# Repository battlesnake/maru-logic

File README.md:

Boolean logic toy for a toddler.

Powered via USB-C (5V) off pretty much any phone charger or other USB-C power source.

Also, I decided to take a "no code" approach to this project, i.e. everything is basically analogue, including the memory and running-LED effects.

[Render](https://github.com/battlesnake/maru-logic/blob/da1b877b9f830693bbb3e6eb010e83701448b195/renders/0001.png)

TODO: Upload the demo video to the repo and add to README

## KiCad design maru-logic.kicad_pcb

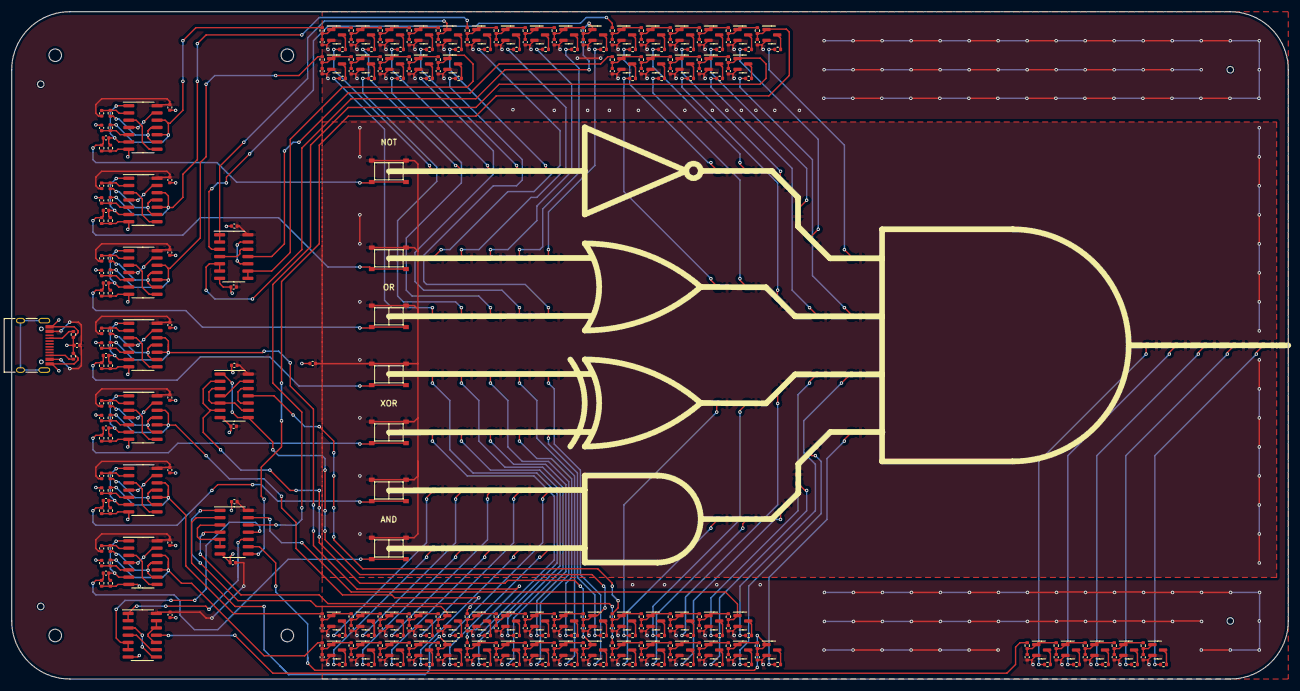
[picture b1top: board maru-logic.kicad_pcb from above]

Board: 2 copper layers, 223.5 x 116.8 mm, 404 parts (0 on the bottom side), 262 nets.

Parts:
C101, C102, C103, C104, C105, C106, C107, C108, C109, C201, C501, C701, C901, C1101, C1301, C1501: 100n; C_0402_1005Metric
C202, C203, C204, C502, C503, C504, C702, C703, C704, C902, C903, C904, C1102, C1103, C1104, C1302, C1303, C1304, C1502, C1503, C1504: 1n; C_0402_1005Metric
C401, C1701, C1801, C1901, C2001, C2101, C2201, C2301, C2401, C2501, C2601, C2701, C2801, C2901, C3001, C3201, C3301, C3401, C3501, C3601, C3701, C3801, C3901, C4001, C4301, C4501, C4601, C4701, C4801, C4901, C5001, C5101, C5201, C5301, C5501, C5601, C5701, C5801, C5901, C6101, C6201, C6301, C6401, C6501, C6701, C6801, C6901, C7001, C7101, C7401, C7501, C7601, C7701, C7801, C8001, C8101, C9801, C9901, C10001, C10101, C10201, C10301: 1u; C_0402_1005Metric
D401, D1701, D1801, D1901, D2001, D2101, D2201, D2301, D2401, D2501, D2601, D2701, D2801, D2901, D3001, D3201, D3301, D3401, D3501, D3601, D3701, D3801, D3901, D4001, D4301, D4501, D4601, D4701, D4801, D4901, D5001, D5101, D5201, D5301, D5501, D5601, D5701, D5801, D5901, D6101, D6201, D6301, D6401, D6501, D6701, D6801, D6901, D7001, D7101, D7401, D7501, D7601, D7701, D7801, D8001, D8101, D9801, D9901, D10001, D10101, D10201, D10301: White; LED_0603_1608Metric_no_silk
H101, H102, H105, H106: JLC; JLCPCB_ToolingHole_1152_1300_1400_1650
H103, H104, H107, H108: MountingHole; MountingHole_2.2mm_M2_ISO7380
J101: USB-C; USB_C_Receptacle_HRO_TYPE-C-31-M-12
Q401, Q1701, Q1801, Q1901, Q2001, Q2101, Q2201, Q2301, Q2401, Q2501, Q2601, Q2701, Q2801, Q2901, Q3001, Q3201, Q3301, Q3401, Q3501, Q3601, Q3701, Q3801, Q3901, Q4001, Q4301, Q4501, Q4601, Q4701, Q4801, Q4901, Q5001, Q5101, Q5201, Q5301, Q5501, Q5601, Q5701, Q5801, Q5901, Q6101, Q6201, Q6301, Q6401, Q6501, Q6701, Q6801, Q6901, Q7001, Q7101, Q7401, Q7501, Q7601, Q7701, Q7801, Q8001, Q8101, Q9801, Q9901, Q10001, Q10101, Q10201, Q10301: 2N7002; SOT-23
R101, R102: 5.1k; R_0402_1005Metric
R201, R501, R701, R901, R1101, R1301, R1501: 1M; R_0402_1005Metric
R202, R502, R702, R902, R1102, R1302, R1502: 1k; R_0402_1005Metric
R203, R204, R503, R504, R703, R704, R903, R904, R1103, R1104, R1303, R1304, R1503, R1504: 10k; R_0402_1005Metric
R401, R1701, R1801, R1901, R2001, R2101, R2201, R2301, R2401, R2501, R2601, R2701, R2801, R2901, R3001, R3201, R3301, R3401, R3501, R3601, R3701, R3801, R3901, R4001, R4301, R4501, R4601, R4701, R4801, R4901, R5001, R5101, R5201, R5301, R5501, R5601, R5701, R5801, R5901, R6101, R6201, R6301, R6401, R6501, R6701, R6801, R6901, R7001, R7101, R7401, R7501, R7601, R7701, R7801, R8001, R8101, R9801, R9901, R10001, R10101, R10201, R10301: 100k; R_0402_1005Metric
R402, R1702, R1802, R1902, R2002, R2102, R2202, R2302, R2402, R2502, R2602, R2702, R2802, R2902, R3002, R3202, R3302, R3402, R3502, R3602, R3702, R3802, R3902, R4002, R4302, R4502, R4602, R4702, R4802, R4902, R5002, R5102, R5202, R5302, R5502, R5602, R5702, R5802, R5902, R6102, R6202, R6302, R6402, R6502, R6702, R6802, R6902, R7002, R7102, R7402, R7502, R7602, R7702, R7802, R8002, R8102, R9802, R9902, R10002, R10102, R10202, R10302: 220; R_0402_1005Metric
SW301, SW601, SW801, SW1001, SW1201, SW1401, SW1601: Push; jlc_pushbutton
U101, U102, U103, U104, U201, U501, U701, U901, U1101, U1301, U1501: 4093; SOIC-14_3.9x8.7mm_P1.27mm

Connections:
/ALL_X: R1801.1, U104.11
/ALL_Y: C2101.1, Q2101.1 (G), R2101.2
/AND_A: C7101.1, Q7101.1 (G), R7101.2, U103.1
/AND_B: C7801.1, Q7801.1 (G), R7801.2, U103.2
/AND_X: R4701.1, U103.4
/AND_Y: C4901.1, Q4901.1 (G), R4901.2, U103.9
/BAA: R504.1, R6901.1, U501.10, U501.12
/BAB: R704.1, R7601.1, U701.10, U701.12
/BNA: R204.1, R2801.1, U201.10, U201.12
/BOA: R904.1, R3601.1, U901.10, U901.12
/BOB: R1104.1, R3901.1, U1101.10, U1101.12
/BXA: R1304.1, R5701.1, U1301.10, U1301.12
/BXB: R1504.1, R6301.1, U1501.10, U1501.12
/Button AND_A/T flip-flop/PULSE: C502.2, R502.2, U501.1, U501.6
/Button AND_A/T flip-flop/Q': C504.1, R504.2, U501.5
/Button AND_A/T flip-flop/RESET: U501.4, U501.13
/Button AND_A/T flip-flop/SET: U501.3, U501.8
/Button AND_A/T flip-flop/TOGGLE: C502.1, R501.2, SW601.2
/Button AND_A/T flip-flop/~Q: R503.1, U501.9, U501.11
/Button AND_A/T flip-flop/~Q': C503.2, R503.2, U501.2
/Button AND_B/T flip-flop/PULSE: C702.2, R702.2, U701.1, U701.6
/Button AND_B/T flip-flop/Q': C704.1, R704.2, U701.5
/Button AND_B/T flip-flop/RESET: U701.4, U701.13
/Button AND_B/T flip-flop/SET: U701.3, U701.8
/Button AND_B/T flip-flop/TOGGLE: C702.1, R701.2, SW801.2
/Button AND_B/T flip-flop/~Q: R703.1, U701.9, U701.11
/Button AND_B/T flip-flop/~Q': C703.2, R703.2, U701.2
/Button NOT_A/T flip-flop/PULSE: C202.2, R202.2, U201.1, U201.6
/Button NOT_A/T flip-flop/Q': C204.1, R204.2, U201.5
/Button NOT_A/T flip-flop/RESET: U201.4, U201.13
/Button NOT_A/T flip-flop/SET: U201.3, U201.8
/Button NOT_A/T flip-flop/TOGGLE: C202.1, R201.2, SW301.2
/Button NOT_A/T flip-flop/~Q: R203.1, U201.9, U201.11
/Button NOT_A/T flip-flop/~Q': C203.2, R203.2, U201.2
/Button OR_A/T flip-flop/PULSE: C902.2, R902.2, U901.1, U901.6
/Button OR_A/T flip-flop/Q': C904.1, R904.2, U901.5
/Button OR_A/T flip-flop/RESET: U901.4, U901.13
/Button OR_A/T flip-flop/SET: U901.3, U901.8
/Button OR_A/T flip-flop/TOGGLE: C902.1, R901.2, SW1001.2
/Button OR_A/T flip-flop/~Q: R903.1, U901.9, U901.11
/Button OR_A/T flip-flop/~Q': C903.2, R903.2, U901.2
/Button OR_B/T flip-flop/PULSE: C1102.2, R1102.2, U1101.1, U1101.6
/Button OR_B/T flip-flop/Q': C1104.1, R1104.2, U1101.5
/Button OR_B/T flip-flop/RESET: U1101.4, U1101.13
/Button OR_B/T flip-flop/SET: U1101.3, U1101.8
/Button OR_B/T flip-flop/TOGGLE: C1102.1, R1101.2, SW1201.2
/Button OR_B/T flip-flop/~Q: R1103.1, U1101.9, U1101.11
/Button OR_B/T flip-flop/~Q': C1103.2, R1103.2, U1101.2
/Button XOR_A/T flip-flop/PULSE: C1302.2, R1302.2, U1301.1, U1301.6
/Button XOR_A/T flip-flop/Q': C1304.1, R1304.2, U1301.5
/Button XOR_A/T flip-flop/RESET: U1301.4, U1301.13
/Button XOR_A/T flip-flop/SET: U1301.3, U1301.8
/Button XOR_A/T flip-flop/TOGGLE: C1302.1, R1301.2, SW1401.2
/Button XOR_A/T flip-flop/~Q: R1303.1, U1301.9, U1301.11
/Button XOR_A/T flip-flop/~Q': C1303.2, R1303.2, U1301.2
/Button XOR_B/T flip-flop/PULSE: C1502.2, R1502.2, U1501.1, U1501.6
/Button XOR_B/T flip-flop/Q': C1504.1, R1504.2, U1501.5
/Button XOR_B/T flip-flop/RESET: U1501.4, U1501.13
/Button XOR_B/T flip-flop/SET: U1501.3, U1501.8
/Button XOR_B/T flip-flop/TOGGLE: C1502.1, R1501.2, SW1601.2
/Button XOR_B/T flip-flop/~Q: R1503.1, U1501.9, U1501.11
/Button XOR_B/T flip-flop/~Q': C1503.2, R1503.2, U1501.2
/Chain ALL_X/LINK1: C1801.1, Q1801.1 (G), R401.1, R1801.2
/Chain ALL_X/LINK2: C401.1, Q401.1 (G), R401.2, R1701.1
/Chain ALL_X/LINK3: C1701.1, Q1701.1 (G), R1701.2, R1901.1
/Chain ALL_X/LINK4: C1901.1, Q1901.1 (G), R1901.2, R2101.1
/Chain AND_A/LINK1: C6901.1, Q6901.1 (G), R6701.1, R6901.2
/Chain AND_A/LINK2: C6701.1, Q6701.1 (G), R6701.2, R6801.1
/Chain AND_A/LINK3: C6801.1, Q6801.1 (G), R6801.2, R7001.1
/Chain AND_A/LINK4: C7001.1, Q7001.1 (G), R7001.2, R7101.1
/Chain AND_B/LINK1: C7601.1, Q7601.1 (G), R7401.1, R7601.2
/Chain AND_B/LINK2: C7401.1, Q7401.1 (G), R7401.2, R7501.1
/Chain AND_B/LINK3: C7501.1, Q7501.1 (G), R7501.2, R7701.1
/Chain AND_B/LINK4: C7701.1, Q7701.1 (G), R7701.2, R7801.1
/Chain AND_X/LINK1: C4701.1, Q4701.1 (G), R4601.1, R4701.2
/Chain AND_X/LINK2: C4601.1, Q4601.1 (G), R4501.1, R4601.2
/Chain AND_X/LINK3: C4501.1, Q4501.1 (G), R4501.2, R5001.1
/Chain AND_X/LINK4: C5001.1, Q5001.1 (G), R4801.1, R5001.2
/Chain AND_X/LINK5: C4801.1, Q4801.1 (G), R4801.2, R4901.1
/Chain NOT_A/LINK1: C2801.1, Q2801.1 (G), R2601.1, R2801.2
/Chain NOT_A/LINK2: C2601.1, Q2601.1 (G), R2601.2, R2701.1
/Chain NOT_A/LINK3: C2701.1, Q2701.1 (G), R2701.2, R2901.1
/Chain NOT_A/LINK4: C2901.1, Q2901.1 (G), R2901.2, R3001.1
/Chain NOT_X/LINK1: C9801.1, Q9801.1 (G), R9801.2, R9901.1
/Chain NOT_X/LINK2: C9901.1, Q9901.1 (G), R9901.2, R10001.1
/Chain NOT_X/LINK3: C10001.1, Q10001.1 (G), R10001.2, R10101.1
/Chain NOT_X/LINK4: C10101.1, Q10101.1 (G), R10101.2, R10201.1
/Chain NOT_X/LINK5: C10201.1, Q10201.1 (G), R10201.2, R10301.1
/Chain OR_A/LINK1: C3601.1, Q3601.1 (G), R3401.1, R3601.2
/Chain OR_A/LINK2: C3401.1, Q3401.1 (G), R3401.2, R3501.1
/Chain OR_A/LINK3: C3501.1, Q3501.1 (G), R3501.2, R3701.1
/Chain OR_A/LINK4: C3701.1, Q3701.1 (G), R3701.2, R3801.1
/Chain OR_B/LINK1: C3901.1, Q3901.1 (G), R3201.1, R3901.2
/Chain OR_B/LINK2: C3201.1, Q3201.1 (G), R3201.2, R3301.1
/Chain OR_B/LINK3: C3301.1, Q3301.1 (G), R3301.2, R4001.1
/Chain OR_B/LINK4: C4001.1, Q4001.1 (G), R4001.2, R5301.1
/Chain OR_X/LINK1: C2301.1, Q2301.1 (G), R2001.1, R2301.2
/Chain OR_X/LINK2: C2001.1, Q2001.1 (G), R2001.2, R2201.1
/Chain OR_X/LINK3: C2201.1, Q2201.1 (G), R2201.2, R2401.1
/Chain OR_X/LINK4: C2401.1, Q2401.1 (G), R2401.2, R2501.1
/Chain XOR_A/LINK1: C5701.1, Q5701.1 (G), R5501.1, R5701.2
/Chain XOR_A/LINK2: C5501.1, Q5501.1 (G), R5501.2, R5601.1
/Chain XOR_A/LINK3: C5601.1, Q5601.1 (G), R5601.2, R5801.1
/Chain XOR_A/LINK4: C5801.1, Q5801.1 (G), R5801.2, R5901.1
/Chain XOR_B/LINK1: C6301.1, Q6301.1 (G), R6101.1, R6301.2
/Chain XOR_B/LINK2: C6101.1, Q6101.1 (G), R6101.2, R6201.1
/Chain XOR_B/LINK3: C6201.1, Q6201.1 (G), R6201.2, R6401.1
/Chain XOR_B/LINK4: C6401.1, Q6401.1 (G), R6401.2, R6501.1
/Chain XOR_X/LINK1: C5201.1, Q5201.1 (G), R4301.1, R5201.2
/Chain XOR_X/LINK2: C4301.1, Q4301.1 (G), R4301.2, R5101.1
/Chain XOR_X/LINK3: C5101.1, Q5101.1 (G), R5101.2, R8001.1
/Chain XOR_X/LINK4: C8001.1, Q8001.1 (G), R8001.2, R8101.1
/NOT_A: C3001.1, Q3001.1 (G), R3001.2, U101.1, U101.2
/NOT_X: R9801.1, U101.3
/NOT_Y: C10301.1, Q10301.1 (G), R10301.2, U103.8
/OR_A: C3801.1, Q3801.1 (G), R3801.2, U101.5, U101.6
/OR_B: C5301.1, Q5301.1 (G), R5301.2, U101.8, U101.9
/OR_X: R2301.1, U101.11
/OR_Y: C2501.1, Q2501.1 (G), R2501.2, U103.12
/XOR_A: C5901.1, Q5901.1 (G), R5901.2, U102.2, U102.6
/XOR_B: C6501.1, Q6501.1 (G), R6501.2, U102.1, U102.8
/XOR_X: R5201.1, U102.11
/XOR_Y: C8101.1, Q8101.1 (G), R8101.2, U103.13
unnamed: D401.1 (K), R402.1
unnamed: D1701.1 (K), R1702.1
unnamed: D1801.1 (K), R1802.1
unnamed: D1901.1 (K), R1902.1
unnamed: D2001.1 (K), R2002.1
unnamed: D2101.1 (K), R2102.1
unnamed: D2201.1 (K), R2202.1
unnamed: D2301.1 (K), R2302.1
unnamed: D2401.1 (K), R2402.1
unnamed: D2501.1 (K), R2502.1
unnamed: D2601.1 (K), R2602.1
unnamed: D2701.1 (K), R2702.1
unnamed: D2801.1 (K), R2802.1
unnamed: D2901.1 (K), R2902.1
unnamed: D3001.1 (K), R3002.1
unnamed: D3201.1 (K), R3202.1
unnamed: D3301.1 (K), R3302.1
unnamed: D3401.1 (K), R3402.1
unnamed: D3501.1 (K), R3502.1
unnamed: D3601.1 (K), R3602.1
unnamed: D3701.1 (K), R3702.1
unnamed: D3801.1 (K), R3802.1
unnamed: D3901.1 (K), R3902.1
unnamed: D4001.1 (K), R4002.1
unnamed: D4301.1 (K), R4302.1
unnamed: D4501.1 (K), R4502.1
unnamed: D4601.1 (K), R4602.1
unnamed: D4701.1 (K), R4702.1
unnamed: D4801.1 (K), R4802.1
unnamed: D4901.1 (K), R4902.1
unnamed: D5001.1 (K), R5002.1
unnamed: D5101.1 (K), R5102.1
unnamed: D5201.1 (K), R5202.1
unnamed: D5301.1 (K), R5302.1
unnamed: D5501.1 (K), R5502.1
unnamed: D5601.1 (K), R5602.1
unnamed: D5701.1 (K), R5702.1
unnamed: D5801.1 (K), R5802.1
unnamed: D5901.1 (K), R5902.1
unnamed: D6101.1 (K), R6102.1
unnamed: D6201.1 (K), R6202.1
unnamed: D6301.1 (K), R6302.1
unnamed: D6401.1 (K), R6402.1
unnamed: D6501.1 (K), R6502.1
unnamed: D6701.1 (K), R6702.1
unnamed: D6801.1 (K), R6802.1
unnamed: D6901.1 (K), R6902.1
unnamed: D7001.1 (K), R7002.1
unnamed: D7101.1 (K), R7102.1
unnamed: D7401.1 (K), R7402.1
unnamed: D7501.1 (K), R7502.1
unnamed: D7601.1 (K), R7602.1
unnamed: D7701.1 (K), R7702.1
unnamed: D7801.1 (K), R7802.1
unnamed: D8001.1 (K), R8002.1
unnamed: D8101.1 (K), R8102.1
unnamed: D9801.1 (K), R9802.1
unnamed: D9901.1 (K), R9902.1
unnamed: D10001.1 (K), R10002.1
unnamed: D10101.1 (K), R10102.1
unnamed: D10201.1 (K), R10202.1
unnamed: D10301.1 (K), R10302.1
unnamed: J101.A5 (CC1), R101.1
unnamed: J101.B5 (CC2), R102.1
unnamed: Q401.3 (D), R402.2
unnamed: Q1701.3 (D), R1702.2
unnamed: Q1801.3 (D), R1802.2
unnamed: Q1901.3 (D), R1902.2
unnamed: Q2001.3 (D), R2002.2
unnamed: Q2101.3 (D), R2102.2
unnamed: Q2201.3 (D), R2202.2
unnamed: Q2301.3 (D), R2302.2
unnamed: Q2401.3 (D), R2402.2
unnamed: Q2501.3 (D), R2502.2
unnamed: Q2601.3 (D), R2602.2
unnamed: Q2701.3 (D), R2702.2
unnamed: Q2801.3 (D), R2802.2
unnamed: Q2901.3 (D), R2902.2
unnamed: Q3001.3 (D), R3002.2
unnamed: Q3201.3 (D), R3202.2
unnamed: Q3301.3 (D), R3302.2
unnamed: Q3401.3 (D), R3402.2
unnamed: Q3501.3 (D), R3502.2
unnamed: Q3601.3 (D), R3602.2
unnamed: Q3701.3 (D), R3702.2
unnamed: Q3801.3 (D), R3802.2
unnamed: Q3901.3 (D), R3902.2
unnamed: Q4001.3 (D), R4002.2
unnamed: Q4301.3 (D), R4302.2
unnamed: Q4501.3 (D), R4502.2
unnamed: Q4601.3 (D), R4602.2
unnamed: Q4701.3 (D), R4702.2
unnamed: Q4801.3 (D), R4802.2
unnamed: Q4901.3 (D), R4902.2
unnamed: Q5001.3 (D), R5002.2
unnamed: Q5101.3 (D), R5102.2
unnamed: Q5201.3 (D), R5202.2
unnamed: Q5301.3 (D), R5302.2
unnamed: Q5501.3 (D), R5502.2
unnamed: Q5601.3 (D), R5602.2
unnamed: Q5701.3 (D), R5702.2
unnamed: Q5801.3 (D), R5802.2
unnamed: Q5901.3 (D), R5902.2
unnamed: Q6101.3 (D), R6102.2
unnamed: Q6201.3 (D), R6202.2
unnamed: Q6301.3 (D), R6302.2
unnamed: Q6401.3 (D), R6402.2
unnamed: Q6501.3 (D), R6502.2
unnamed: Q6701.3 (D), R6702.2
unnamed: Q6801.3 (D), R6802.2
unnamed: Q6901.3 (D), R6902.2
unnamed: Q7001.3 (D), R7002.2
unnamed: Q7101.3 (D), R7102.2
unnamed: Q7401.3 (D), R7402.2
unnamed: Q7501.3 (D), R7502.2
unnamed: Q7601.3 (D), R7602.2
unnamed: Q7701.3 (D), R7702.2
unnamed: Q7801.3 (D), R7802.2
unnamed: Q8001.3 (D), R8002.2
unnamed: Q8101.3 (D), R8102.2
unnamed: Q9801.3 (D), R9802.2
unnamed: Q9901.3 (D), R9902.2
unnamed: Q10001.3 (D), R10002.2
unnamed: Q10101.3 (D), R10102.2
unnamed: Q10201.3 (D), R10202.2
unnamed: Q10301.3 (D), R10302.2
unnamed: U101.10, U101.13
unnamed: U101.4, U101.12
unnamed: U102.3, U102.5, U102.9
unnamed: U102.10, U102.12
unnamed: U102.4, U102.13
unnamed: U103.3, U103.5, U103.6
unnamed: U103.10, U104.1, U104.2
unnamed: U103.11, U104.5, U104.6
unnamed: U104.3, U104.8
unnamed: U104.4, U104.9
unnamed: U104.10, U104.12, U104.13
VDD: C101.1, C102.1, C103.1, C104.1, C105.1, C106.1, C107.1, C108.1, C109.1, C201.1, C203.1, C501.1, C503.1, C701.1, C703.1, C901.1, C903.1, C1101.1, C1103.1, C1301.1, C1303.1, C1501.1, C1503.1, D401.2 (A), D1701.2 (A), D1801.2 (A), D1901.2 (A), D2001.2 (A), D2101.2 (A), D2201.2 (A), D2301.2 (A), D2401.2 (A), D2501.2 (A), D2601.2 (A), D2701.2 (A), D2801.2 (A), D2901.2 (A), D3001.2 (A), D3201.2 (A), D3301.2 (A), D3401.2 (A), D3501.2 (A), D3601.2 (A), D3701.2 (A), D3801.2 (A), D3901.2 (A), D4001.2 (A), D4301.2 (A), D4501.2 (A), D4601.2 (A), D4701.2 (A), D4801.2 (A), D4901.2 (A), D5001.2 (A), D5101.2 (A), D5201.2 (A), D5301.2 (A), D5501.2 (A), D5601.2 (A), D5701.2 (A), D5801.2 (A), D5901.2 (A), D6101.2 (A), D6201.2 (A), D6301.2 (A), D6401.2 (A), D6501.2 (A), D6701.2 (A), D6801.2 (A), D6901.2 (A), D7001.2 (A), D7101.2 (A), D7401.2 (A), D7501.2 (A), D7601.2 (A), D7701.2 (A), D7801.2 (A), D8001.2 (A), D8101.2 (A), D9801.2 (A), D9901.2 (A), D10001.2 (A), D10101.2 (A), D10201.2 (A), D10301.2 (A), J101.A4 (VBUS), J101.A9 (VBUS), J101.B4 (VBUS), J101.B9 (VBUS), SW301.1, SW601.1, SW801.1, SW1001.1, SW1201.1, SW1401.1, SW1601.1, U101.14 (VCC), U102.14 (VCC), U103.14 (VCC), U104.14 (VCC), U201.14 (VCC), U501.14 (VCC), U701.14 (VCC), U901.14 (VCC), U1101.14 (VCC), U1301.14 (VCC), U1501.14 (VCC)
VSS: C101.2, C102.2, C103.2, C104.2, C105.2, C106.2, C107.2, C108.2, C109.2, C201.2, C204.2, C401.2, C501.2, C504.2, C701.2, C704.2, C901.2, C904.2, C1101.2, C1104.2, C1301.2, C1304.2, C1501.2, C1504.2, C1701.2, C1801.2, C1901.2, C2001.2, C2101.2, C2201.2, C2301.2, C2401.2, C2501.2, C2601.2, C2701.2, C2801.2, C2901.2, C3001.2, C3201.2, C3301.2, C3401.2, C3501.2, C3601.2, C3701.2, C3801.2, C3901.2, C4001.2, C4301.2, C4501.2, C4601.2, C4701.2, C4801.2, C4901.2, C5001.2, C5101.2, C5201.2, C5301.2, C5501.2, C5601.2, C5701.2, C5801.2, C5901.2, C6101.2, C6201.2, C6301.2, C6401.2, C6501.2, C6701.2, C6801.2, C6901.2, C7001.2, C7101.2, C7401.2, C7501.2, C7601.2, C7701.2, C7801.2, C8001.2, C8101.2, C9801.2, C9901.2, C10001.2, C10101.2, C10201.2, C10301.2, J101.A1 (GND), J101.A12 (GND), J101.B1 (GND), J101.B12 (GND), Q401.2 (S), Q1701.2 (S), Q1801.2 (S), Q1901.2 (S), Q2001.2 (S), Q2101.2 (S), Q2201.2 (S), Q2301.2 (S), Q2401.2 (S), Q2501.2 (S), Q2601.2 (S), Q2701.2 (S), Q2801.2 (S), Q2901.2 (S), Q3001.2 (S), Q3201.2 (S), Q3301.2 (S), Q3401.2 (S), Q3501.2 (S), Q3601.2 (S), Q3701.2 (S), Q3801.2 (S), Q3901.2 (S), Q4001.2 (S), Q4301.2 (S), Q4501.2 (S), Q4601.2 (S), Q4701.2 (S), Q4801.2 (S), Q4901.2 (S), Q5001.2 (S), Q5101.2 (S), Q5201.2 (S), Q5301.2 (S), Q5501.2 (S), Q5601.2 (S), Q5701.2 (S), Q5801.2 (S), Q5901.2 (S), Q6101.2 (S), Q6201.2 (S), Q6301.2 (S), Q6401.2 (S), Q6501.2 (S), Q6701.2 (S), Q6801.2 (S), Q6901.2 (S), Q7001.2 (S), Q7101.2 (S), Q7401.2 (S), Q7501.2 (S), Q7601.2 (S), Q7701.2 (S), Q7801.2 (S), Q8001.2 (S), Q8101.2 (S), Q9801.2 (S), Q9901.2 (S), Q10001.2 (S), Q10101.2 (S), Q10201.2 (S), Q10301.2 (S), R101.2, R102.2, R201.1, R202.1, R501.1, R502.1, R701.1, R702.1, R901.1, R902.1, R1101.1, R1102.1, R1301.1, R1302.1, R1501.1, R1502.1, U101.7 (GND), U102.7 (GND), U103.7 (GND), U104.7 (GND), U201.7 (GND), U501.7 (GND), U701.7 (GND), U901.7 (GND), U1101.7 (GND), U1301.7 (GND), U1501.7 (GND)

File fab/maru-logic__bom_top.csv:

"Comment","Designator","Footprint","LCSC Part Number"
"1k","R1102 R1302 R1502 R202 R502 R702 R902","0402","C11702"
"1n","C1102 C1103 C1104 C1302 C1303 C1304 C1502 C1503 C1504 C202 C203 C204 C502 C503 C504 C702 C703 C704 C902 C903 C904","0402","C1523"
"100n","C101 C102 C103 C104 C105 C106 C107 C108 C109 C1101 C1301 C1501 C201 C501 C701 C901","0402","C1525"
"USB-C","J101","USB_C_Receptacle_HRO_TYPE-C-31-M-12","C165948"
"4093","U101 U102 U103 U104 U1101 U1301 U1501 U201 U501 U701 U901","SOIC-14_3.9x8.7mm_P1.27mm","C194332"
"White","D10001 D10101 D10201 D10301 D1701 D1801 D1901 D2001 D2101 D2201 D2301 D2401 D2501 D2601 D2701 D2801 D2901 D3001 D3201 D3301 D3401 D3501 D3601 D3701 D3801 D3901 D4001 D401 D4301 D4501 D4601 D4701 D4801 D4901 D5001 D5101 D5201 D5301 D5501 D5601 D5701 D5801 D5901 D6101 D6201 D6301 D6401 D6501 D6701 D6801 D6901 D7001 D7101 D7401 D7501 D7601 D7701 D7801 D8001 D8101 D9801 D9901","LED_0603_1608Metric_no_silk","C2290"
"220","R10002 R10102 R10202 R10302 R1702 R1802 R1902 R2002 R2102 R2202 R2302 R2402 R2502 R2602 R2702 R2802 R2902 R3002 R3202 R3302 R3402 R3502 R3602 R3702 R3802 R3902 R4002 R402 R4302 R4502 R4602 R4702 R4802 R4902 R5002 R5102 R5202 R5302 R5502 R5602 R5702 R5802 R5902 R6102 R6202 R6302 R6402 R6502 R6702 R6802 R6902 R7002 R7102 R7402 R7502 R7602 R7702 R7802 R8002 R8102 R9802 R9902","0402","C25091"
"100k","R10001 R10101 R10201 R10301 R1701 R1801 R1901 R2001 R2101 R2201 R2301 R2401 R2501 R2601 R2701 R2801 R2901 R3001 R3201 R3301 R3401 R3501 R3601 R3701 R3801 R3901 R4001 R401 R4301 R4501 R4601 R4701 R4801 R4901 R5001 R5101 R5201 R5301 R5501 R5601 R5701 R5801 R5901 R6101 R6201 R6301 R6401 R6501 R6701 R6801 R6901 R7001 R7101 R7401 R7501 R7601 R7701 R7801 R8001 R8101 R9801 R9901","0402","C25741"
"10k","R1103 R1104 R1303 R1304 R1503 R1504 R203 R204 R503 R504 R703 R704 R903 R904","0402","C25744"
"5.1k","R101 R102","0402","C25905"
"1M","R1101 R1301 R1501 R201 R501 R701 R901","0402","C26083"
"Push","SW1001 SW1201 SW1401 SW1601 SW301 SW601 SW801","jlc_pushbutton","C318884"
"1u","C10001 C10101 C10201 C10301 C1701 C1801 C1901 C2001 C2101 C2201 C2301 C2401 C2501 C2601 C2701 C2801 C2901 C3001 C3201 C3301 C3401 C3501 C3601 C3701 C3801 C3901 C4001 C401 C4301 C4501 C4601 C4701 C4801 C4901 C5001 C5101 C5201 C5301 C5501 C5601 C5701 C5801 C5901 C6101 C6201 C6301 C6401 C6501 C6701 C6801 C6901 C7001 C7101 C7401 C7501 C7601 C7701 C7801 C8001 C8101 C9801 C9901","0402","C52923"
"2N7002","Q10001 Q10101 Q10201 Q10301 Q1701 Q1801 Q1901 Q2001 Q2101 Q2201 Q2301 Q2401 Q2501 Q2601 Q2701 Q2801 Q2901 Q3001 Q3201 Q3301 Q3401 Q3501 Q3601 Q3701 Q3801 Q3901 Q4001 Q401 Q4301 Q4501 Q4601 Q4701 Q4801 Q4901 Q5001 Q5101 Q5201 Q5301 Q5501 Q5601 Q5701 Q5801 Q5901 Q6101 Q6201 Q6301 Q6401 Q6501 Q6701 Q6801 Q6901 Q7001 Q7101 Q7401 Q7501 Q7601 Q7701 Q7801 Q8001 Q8101 Q9801 Q9901","SOT-23","C8545"

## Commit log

2022-11-21 Initial
2022-11-22 routing done
2022-11-22 remove empty sheets
2022-11-24 ready to order
2022-11-27 case design rev1 complete
2022-11-27 packed blend, updated gitignore
2022-11-27 added renders and production files for case
2022-12-10 started fixing issues from V1
2022-12-12 pre-re-layout
2022-12-13 sim for LED timings with gate in between
2022-12-13 pcb-text plugin applied, next step is to write a replicate layout plugin that actually works
2022-12-17 safe
2022-12-20 about to run my plugin now
2022-12-20 cloned
2022-12-25 layout done, starting case
2022-12-26 v2 order files
2023-01-04 updated models
